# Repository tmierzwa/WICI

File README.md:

<p align="center"><picture><source media="(prefers-color-scheme: dark)" srcset="media/logo/WICI-na-ciemnym.svg"></picture></p>

<h1 align="center">Łączność awaryjna, gdy milkną telefony</h1>

Gdy nie ma prądu, zasięgu komórkowego ani internetu, ludzie w schronieniu nadal muszą dać znać, że brakuje wody, ktoś potrzebuje lekarza albo trzeba kogoś przewieźć. **WICI to otwarty projekt stacji radiowej do takich krótkich zgłoszeń i odpowiedzi.** Stacje mają stać tam, gdzie w kryzysie gromadzą się ludzie, i łączyć się ze stanowiskiem odbiorczym, które wyznacza gmina.

Gospodarz schronienia wybiera na ekranie stacji kategorię potrzeby i liczbę osób, a stacja wysyła zgłoszenie radiem. Na ekranie widać potem, czy odbiorca zgłoszenie zapisał, czy dyżurny je przeczytał i czy zapadła decyzja o pomocy. Każda włączona stacja przekazuje też wiadomości sąsiednich stacji, więc zgłoszenia docierają dalej niż zasięg jednego radia.

<p align="center"><sub>Wizualizacja koncepcyjna stacji według dzisiejszych założeń; <a href="hardware/obudowa/README.md">obudowa i render</a>, <a href="hardware/obudowa/render/stacja-materialy.png">pełna rozdzielczość</a>.</sub></p>

Stację można wypróbować w przeglądarce. [Symulator](https://wici.net.pl/symulator/) uruchamia ten sam program, który ma działać w prawdziwej stacji, razem z ćwiczeniami dla gospodarza i stanowiskiem odbiorczym. Uwagi można zgłosić przyciskiem „Zgłoś uwagę” w symulatorze albo [formularzem](https://github.com/tmierzwa/WICI/issues/new?template=uwaga-symulator.yml).

**Projekt jest na etapie prototypu (wersja 0.5). Dwa prototypy stacji są w montażu, a żadnej stacji nie sprawdzono jeszcze w terenie.** Dokumentacja, obliczenia i kod są otwarte. Pełny opis pomysłu, scenariuszy i ograniczeń jest na stronie [wici.net.pl](https://wici.net.pl/).

## Jak to ma działać

Stacja ma ekran, przyciski, antenę i ogniwa AA. Na ogniwach ma pracować co najmniej 48 godzin, a ze źródła 12 V dłużej. Zasięg i czas pracy trzeba jeszcze potwierdzić pomiarami.

W schronieniu stacja działa sama, bez komputera. Później będzie można podłączyć do niej laptop z wygodniejszym panelem, a przez router Wi-Fi udostępnić mieszkańcom lokalną stronę do zgłoszeń z telefonu, bez instalowania aplikacji. Na stanowisku odbiorczym komputer jest obowiązkowy: dyżurny przyjmuje na nim zgłoszenia i przekazuje je służbom.

Sieć trzeba przygotować z gminą i służbami przed kryzysem: zamontować anteny, sprawdzić trasy radiowe i uzgodnić dyżury. WICI ma uzupełniać lokalny system ochrony ludności. Nie zastępuje numeru 112 ani organizacji pomocy.

Pilotaż ma się odbyć na stacjach z ESP32-S3 i radiem LoRa SX1262, w profilu LoRa SF7 na kanale 869,525 MHz. Własny profil radiowy P1 (układy CC1120 i S2-LP), stanowiska deweloperskie i projekt własnej płytki R02 wstrzymano 8 października 2026 r. (F99); opisuje je [archiwum](docs/archiwum/README.md).

## Gdzie jesteśmy

Stan na 9 listopada 2026 r. Plan ma osiem kroków, a każdy ma warunek wejścia i wynik ([kolejność prac](docs/concept/08-plan-weryfikacji-i-decyzje.html#kolejnosc-prac)).

- **Krok 1, radia testowe: wykonany.** Dwa gotowe zestawy Seeed 102010611 (XIAO ESP32-S3 z Wio SX1262) wymieniły przy stole 100 ze 100 ramek w obie strony. W budynku, przy mocy 0 dBm, trasa około 20 m przez dwie ściany też dała 100/100, a dwie trudniejsze trasy były na granicy zasięgu tego profilu ([wyniki](hardware/radio-pair/evidence/range-r0-2026-10-10.txt)). Od 2 listopada te same zestawy z obrazem `xiao` służą do prób protokołu łącza WICI-Link v3 przy stole ([procedura](hardware/xiao-wici/README.md)).
- **Krok 2, radia RNode przy stole: wykonany.** 2 listopada dwa zestawy RAK19007 z RAK4631 (nRF52840 i SX1262) z oficjalnym firmware RNode 1.86 i Reticulum w Pythonie przeszły po 10 z 10 prób `rnprobe` w każdą stronę, w SF7 i w SF8. IFAC odrzucił radio z innym hasłem ([wyniki](hardware/rnode/evidence/krok2-2026-11-02.txt)). Wgranie firmware wymagało dwóch obejść ([radia RNode](hardware/rnode/README.md)). Obie instancje Reticulum działały na jednym laptopie, a jedyną drogą między nimi było radio. Zostały pomiar mocy na złączu przy 13 dBm i sprawdzenie, co RNode robi po przekroczeniu limitu czasu nadawania. Te same radia posłużą do pomiaru zasięgu (kroki 3 i 5) i do sprawdzenia zgodności prototypu (krok 4).
- **Krok 4, prototyp na płytce v1: w montażu.** Pięć płytek v1 (dawniej N1) z JLCPCB, części, panele i moduły autor kupił sam ([zamówienie](hardware/dev-bench/przed-produkcja.md#zamówienie-2026-10-10-l0)). Dwie płytki z zamontowanym SMD są u wykonawcy, [pw-lab.pl](https://pw-lab.pl/), który montuje i uruchamia je według [zlecenia](hardware/l0-diagnostic/ZLECENIE.md) i [instrukcji z diagnozą usterek](hardware/l0-diagnostic/MONTAZ-I-TESTY.md); trzy płytki są gołe. Najpierw powstanie jeden prototyp z programem diagnostycznym `l0-0.5`, drugi dopiero po udanym uruchomieniu pierwszego. Montaż pierwszego zaczął się 27 października i pokazał, że taśma panelu nie mieści się w obrysie płytki (F118). Panel mocuje się poza obrysem. Pierwsza sztuka (P001) jest zmontowana od 1 listopada i przeszła u wykonawcy pierwsze pomiary programem diagnostycznym (szyny zasilania, magistrala SPI, prąd nadawania); jego uwagi weszły do instrukcji. Poprawiony projekt v1.1 jest na `main`; nie jest do zamówienia, bo służy jako baza dla v2.
- **Program stacji.** Obrazy stacji mają własny rdzeń Reticulum z LXMF ([opis](firmware/reticulum-core.md)). Rdzeń jest domyślny, a port microReticulum zostaje w osobnych obrazach `*-port` do etapu rdzenia 6-5, który go usunie. Sprawdzono go na komputerze (zgodność z Reticulum i LXMF w Pythonie, fuzzing), ale nie na płytce. Próby 1–8 na płytkach są warunkiem pilotażu i wydania, ale nie scalania zmian. Obraz `l0` (`l0-0.6`, z portem `l0-port`, `l0-0.7`) ma własny sterownik SX1262 w profilu LoRa pilotażu, polecenia pomiarowe i tryb pracy do badań EMC ([opis](firmware/docs/prototyp-l0-i-xiao.md#stacja-l0-l0)); na płytce jeszcze nie działał. Interfejs LoRa w stosie Reticulum, zgodny z radiem RNode, przechodzi próby na komputerze z `RNodeInterface` przez emulator radia ([zgłoszenie 22](https://github.com/tmierzwa/WICI/issues/22)); próba z radiem RNode na prototypie jest w kroku 4. Od 2 listopada program ma też własny protokół łącza [WICI-Link v3](docs/spec/wici-link.md), który ma zastąpić Reticulum jako domyślny nośnik w sieci stacji, jeśli spełni warunek decyzji D21 ([warunek przyjęcia](docs/spec/transport.md#warunek-przyjęcia)). Na dwóch zestawach XIAO, przez jeden przeskok, 50 z 50 zgłoszeń dostało RECEIVED w około 5,5 min, bez ponowień ([wyniki](hardware/xiao-wici/evidence/xiao-zestaw-2026-11-03.md)). D21 rozstrzygnie próba na RAK4631 i prototypie. Brakuje funkcji potrzebnych przed pierwszymi stacjami w terenie ([zgłoszenie 23](https://github.com/tmierzwa/WICI/issues/23)).
- **Kroki 5–8.** Stacje pilotażowe powstaną na płytce v2 z linii prototypu (ESP32-S3-DevKitC, Wio SX1262, panel Sharp, FRAM, przyciski) z dodanym torem zasilania z ogniw AA i z 12 V: osiem stacji zamawianych w pełni zmontowanych w JLC, z modułami, obudową i anteną poza zamówieniem. Przed pracą w terenie zespół bada je według norm zharmonizowanych (D20). Wstępny schemat i rozmieszczenie v2 już są ([płytka v2](hardware/plytka-v2/README.md)), a sprawność przetwornicy 3,3 V sprawdzi osobna [płytka testowa](hardware/przetwornica-3v3/README.md); projekt v2 zamyka się po kroku 4. Pomiar w gminie (krok 5) wymaga gminy pilotażowej i wskazanych budynków. Pilotaż trwa co najmniej 3 miesiące, w tym zimę. O wyrobie, czyli stacji WICI, decyduje się po pilotażu.

Zakres prototypu (przygotowany do wyceny, dziś podstawa zlecenia montażu) i zasady wyboru dokumentów opisują [dokumenty przygotowania testów](output/README.md). Instrukcje bieżących prób są w katalogu [hardware](hardware/README.md).

### Kolejność prac

| Krok | Co | Stan |
|---|---|---|
| 1. Radia testowe | wstępna próba radia | wykonany |
| 2. Radia RNode przy stole | RNode na dwóch RAK4631, Reticulum na laptopach, `rnprobe` | wykonany |
| 3. Pomiar ogólny | zasięg na własnym terenie, SF7 i SF8, 13 dBm | do zrobienia |
| 4. Prototyp na płytce v1 | odbiór, program stacji, interfejs LoRa, zgodność z RNode, próby 1–8 rdzenia | w montażu |
| 5. Pomiar w gminie | trzy połączenia, dzień i wieczór | wymaga gminy i kroku 3 |
| 6. Stacje pilotażowe na płytce v2 | projekt v2, 8 stacji (pierwsze 2 jako prototypy v2), badania zgodności na wersji ostatecznej | po kroku 4 |
| 7. Pilotaż | ćwiczenie przy stole, potem ≥3 miesiące pracy | po kroku 6 |
| 8. Wyrób | stacja WICI | decyzja po pilotażu |

Kroki 3 i 4 idą równolegle. Do gminy nie jedzie się z niesprawdzonym sprzętem, więc gmina wchodzi w kroku 5. Pełny opis, z warunkami wejścia i wynikami, jest w [rozdziale 08 koncepcji](docs/concept/08-plan-weryfikacji-i-decyzje.html#kolejnosc-prac).

## Partnerzy projektu

- [pw-lab.pl](https://pw-lab.pl/): montaż, testy oraz diagnoza usterek prototypu stacji.

Firmy, gminy i organizacje, które chcą pomóc sprzętem, próbami albo wiedzą, mogą pisać na [kontakt@wici.net.pl](mailto:kontakt@wici.net.pl).

## Jak możesz pomóc

Najbliższy cel to pomiar zasięgu radiami RNode, a równolegle odbiór prototypu i pierwsza wymiana zgłoszeń z radiem RNode. Potem próby w prawdziwych miejscach. Przyda się doświadczenie w radiu i antenach, w programowaniu ESP32-S3 i SX1262 oraz w organizacji pomocy w gminie.

Można też pomóc bez sprzętu: sprawdzić obliczenia zasięgu, energii i ruchu radiowego, uprościć kartę obsługi albo poprawić tłumaczenia, zwłaszcza ukraińskie.

Konkretne zadania opisuje [CONTRIBUTING.md](CONTRIBUTING.md#od-czego-zacząć). Jeśli chcesz podjąć któreś z nich albo zgłosić błąd, otwórz [zgłoszenie (Issue)](https://github.com/tmierzwa/WICI/issues). Drobne poprawki możesz od razu przesłać jako PR.

## Co jest w repozytorium

| Katalog | Zawartość |
|---|---|
| [docs/concept](docs/concept/index.html) | Koncepcja: potrzeby, scenariusze, dostępne rozwiązania, architektura, wykonalność, zagrożenia, plan prób i otwarte decyzje; [strona online](https://wici.net.pl/) |
| [docs/spec](docs/README.md) | Specyfikacja stacji, warunki odbioru i lista części |
| [firmware](firmware/README.md) | Program stacji ze stosem Reticulum (własny rdzeń z LXMF) dla prototypu (`l0`: ESP32-S3-DevKitC-1 + Wio-SX1262 na płytce v1, profil LoRa); obrazy `bench-*` wstrzymanego wariantu (stanowiska deweloperskie, profil P1) i obrazy `*-port` z portem microReticulum; skompilowane, jeszcze nie uruchomione na sprzęcie |
| [software/reference](software/reference/README.md) | Model wiadomości i potwierdzeń z testami; obliczenia zasięgu, energii i czasu nadawania |
| [software/laptop](software/laptop/README.md) | Aplikacja laptopa z pamięci USB (Windows, macOS, Linux): przygotowanie stacji przez USB (etap 1) i zaszyfrowana baza (etap 2, warstwa bazy); [plan](software/laptop/PLAN.md) kolejnych etapów |
| [software/simulator](software/simulator/README.md) | Symulator stacji w przeglądarce: obraz bench-b oprogramowania stacji (te same źródła i flagi) na wirtualnej płytce ESP32-S3 z emulacją S2-LP, FRAM i Sharp, węzeł i stanowisko odbiorcze, panel płytki v1 (dawniej N1) i dawnej płytki R02 w skali, ćwiczenia gospodarza; [online](https://wici.net.pl/symulator/) |
| [hardware](hardware/README.md) | Radia testowe (`radio-pair`), program diagnostyczny prototypu (`l0-diagnostic`), płytka v1 prototypu (`dev-bench`), obudowa oraz projekt R02 (wstrzymany; materiał do płytki v2 i do wyrobu) |
| [media/film](media/film/README.md) | Dwa filmy o projekcie: około 4,5 min i 60 s |
| [media/infografika](media/infografika/README.md) | Infografika do mediów społecznościowych: post i Stories (PL, EN) |
| [media/logo](media/logo/README.md) | Znak WICI i ikony |
| [tools](docs/development.md) | Kontrola repozytorium i tworzenie paczki źródłowej |

Do sprawdzenia repozytorium wystarczy Python 3.12 lub nowszy:

```sh
python3 -m unittest discover -s software/reference -v
python3 -m unittest discover -s tests -v
python3 tools/verify_repository.py
```

Te same kontrole uruchamia się przed zgłoszeniem zmiany (PR); szczegóły są w [CONTRIBUTING.md](CONTRIBUTING.md#kontrole-przed-pr). Środowisko CAD opisuje [docs/development.md](docs/development.md).

## Kto za tym stoi

Projekt prowadzi na razie jedna osoba: [@tmierzwa](https://github.com/tmierzwa). Gminy, służby, krótkofalowcy i media mogą pisać na [kontakt@wici.net.pl](mailto:kontakt@wici.net.pl). Sprawy techniczne najlepiej zgłaszać w [Issues](https://github.com/tmierzwa/WICI/issues).

Duża część analiz, obliczeń i dokumentacji powstała z pomocą asystenta AI (Claude). Takie commity mają wiersz `Co-Authored-By`. Autor przegląda każdą zmianę. Obliczenia i założenia prawne czekają na niezależny przegląd, a wyniki modelu trzeba potwierdzić pomiarami.

## Licencje

Projekt jest otwarty, a licencje dopuszczają zastosowania komercyjne. Kod jest na licencji MIT, konstrukcja na CERN-OHL-P-2.0, a dokumentacja na CC-BY-4.0.

Wyjątkiem jest rdzeń Reticulum stacji (`firmware/lib/reticulum_core/`). Jako utwór zależny od Reticulum jest na [licencji Reticulum](LICENSES/LicenseRef-Reticulum.txt). Ta licencja dodaje do warunków MIT zakaz użycia w systemach, których funkcją jest celowe szkodzenie ludziom, i zakaz użycia przy tworzeniu zbiorów do trenowania AI, więc nie jest licencją open source w rozumieniu OSI. Obraz stacji z rdzeniem podlega jej jako całość.

Szczegóły są w [LICENSE.md](LICENSE.md). Podatności zgłaszaj prywatnie według [SECURITY.md](SECURITY.md). Obowiązuje [kodeks postępowania](CODE_OF_CONDUCT.md).

## In English

WICI is an open project for an emergency radio station for shelters in Poland. It is meant to carry short requests for help when power, mobile networks and the internet are down. A station with a screen, buttons and AA cells would send requests, show acknowledgements and decisions, and relay neighbouring stations' messages. The receiving post needs a computer and an agreed procedure for passing requests to emergency services.

The project is at the **prototype stage (0.5)**: two prototypes are being assembled by a contractor, and no station has been field-tested. The plan has eight steps. Two RNode radios (RAK4631) were ordered on 29 October 2026 for bench tests and range measurements with Reticulum on two laptops; next come the prototype on the v1 board, a measurement in a municipality, eight pilot stations on a v2 board (ESP32-S3 module with an SX1262 LoRa radio) and a pilot of at least three months, including winter. The project's own FSK profile and custom board were put on hold on 8 October 2026. Range and battery life remain to be measured. Code, hardware and documentation are under permissive licences; the station's Reticulum core is under the Reticulum License, which is not OSI open source (see [LICENSE.md](LICENSE.md)).

One person currently maintains the project with AI assistance. Project partner: [pw-lab.pl](https://pw-lab.pl/), assembly, testing and fault diagnosis of the station prototype. Help with radio, firmware, civil protection, field testing and independent review is welcome. Documentation is in Polish; issues and pull requests in English are welcome. See [CONTRIBUTING.md](CONTRIBUTING.md#in-english). Contact: [kontakt@wici.net.pl](mailto:kontakt@wici.net.pl).

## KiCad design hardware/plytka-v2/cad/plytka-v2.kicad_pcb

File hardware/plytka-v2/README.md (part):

# WICI: płytka v2, schemat wstępny

**Status 2026-11-11: komplet ścieżek z czystym DRC po trzech niezależnych przeglądach ([Ścieżki](#ścieżki-2026-11-10)), pliki produkcyjne po końcowym przeglądzie i sprawdzeniu podglądu JLC ([Części w JLC i pliki produkcyjne](#części-w-jlc-i-pliki-produkcyjne-2026-11-10)). Zamówienie dwóch prototypów czeka na pomiar przetwornicy 3,3 V ([Przed zamówieniem](#przed-zamówieniem)); przymiarka z prawdziwą skrzynką odbędzie się po zamówieniu prototypów, z ryzykiem poprawki rozmieszczenia w następnej wersji. Pierwsze uruchomienie: [uruchomienie.md](uruchomienie.md).** Schemat zbiera w jednym projekcie KiCad płytkę v1.1 prototypu i tor zasilania stacji pilotażowej ([elektronika](../../docs/spec/elektronika.md#stacja-pilotażowa)). Wartości elementów pochodzą z [projektu zasilania](../r02/zasilanie.md) i z [płytki testowej przetwornicy](../przetwornica-3v3/README.md). Obrys i rozmieszczenie są wstępne. Obrys, otwory i złącza na dolnej krawędzi są dopasowane do modelu STEP obudowy Hammond 1599KBAT ([Dopasowanie do obudowy](#dopasowanie-do-obudowy-2026-11-09)). Przymiarka, pomiary na prototypach i krok 4 mogą jeszcze zmienić rozmieszczenie w następnej wersji ([Przed zamówieniem](#przed-zamówieniem)).

| Plik | Zawartość |
|---|---|
| [schemat.pdf](schemat.pdf) | schemat (arkusz A0, połączenia przez etykiety sieci, jak w v1) |
| [polaczenia.md](polaczenia.md) | sygnały MCU i wszystkie sieci |
| [uruchomienie.md](uruchomienie.md) | pierwsze uruchomienie zmontowanego prototypu krok po kroku, z warunkami przerwania |
| [bom.csv](bom.csv) | lista części z producentami, numerami i numerami LCSC, tam gdzie są już wybrane |
| `cad/plytka-v2.kicad_sch`, `cad/plytka-v2.kicad_pcb`, `cad/plytka-v2.kicad_dru` | projekt KiCad 10.0.6: schemat, płytka 4-warstwowa ze ścieżkami i reguły projektu |
| `checks/erc.json`, `checks/netlist.xml`, `checks/drc.json` | ERC (0 naruszeń), lista połączeń i DRC (0 naruszeń poza sitodrukiem, 0 niepołączonych; [Ścieżki](#ścieżki-2026-11-10)) |
| `checks/routing*.dsn`, `checks/routing*.ses`, `checks/routing*.ses.sha256`, `checks/routing*.log`, `checks/routing-anchors.json` | dla każdego etapu routera: zadanie dla Freeroutingu, zachowana sesja ścieżek, suma zadania, z którego powstała, i dziennik przebiegu; lista punktów, w których router może dołączyć do miedzi ręcznej |
| [render-sciezki-gora.png](render-sciezki-gora.png), [render-sciezki-spod.png](render-sciezki-spod.png) | render płytki ze ścieżkami od góry i od spodu |
| `tools/design.py` | jedyne źródło: części, piny, sieci i sprawdzenia przydziału pinów |
| `tools/make_pcb.py` | obrys, otwory i rozmieszczenie: założenia, położenia stałe i obszary bloków |
| `tools/route_pcb.py`, `tools/route.sh` | klasy sieci, reguły, warstwy, miedź ręczna i płaszczyzny, zadania dla routera; uruchomienie Freeroutingu etapami |

Odtworzenie: `hardware/plytka-v2/tools/build.sh` (KiCad 10.0.6). Skrypt sprawdza przydział pinów, generuje schemat, BOM i listę połączeń, uruchamia ERC, rysuje PDF, rozmieszcza elementy na płytce, dokłada miedź ręczną, wczytuje zachowaną sesję ścieżek (gdy pasuje do zadania) i uruchamia DRC. Plików w `cad/` nie edytuje się ręcznie.

## Co zmienia się względem v1.1

| Blok | v1.1 (prototyp L0) | v2 |
|---|---|---|
| MCU | DevKitC w J5/J6, zasilana z USB | ta sama DevKitC v1.1 (N8R8) w J5/J6, zasilana przez piny 3V3 z przetwornicy; pin 5V wolny |
| Radio | Wio na przewodach obok płytki | Wio w gniazdach J8/J9 (2 × 1x7, 2,54 mm), zasilanie przez zworkę pomiarową JP3, przy module C1, C2 i RXEN 10 kΩ (R64); SCK za R18, jak ekran i FRAM |
| Gniazda TI, ST, Nordic | J1–J4, J9, J10, JP3, R17, otwory Arduino | wypadają |
| USB do laptopa | złącze micro USB DevKitC | gniazdo USB-C J4 bez zasilania z VBUS (VBUS tylko na bramkę Q12 wykrywania laptopa), CC1 i CC2 przez 5,1 kΩ, ochrona ESD U8 |
| Ekran, FRAM, dioda | bez zmian | bez zmian (te same oznaczenia) |
| Przyciski i CISZA | B3F na płytce (SW1–SW4), przełącznik na płytce (SW5) | panelowe PV6F240SS i 100SP1T8B13M1QEH z osłoną GT-4R na wiązkach do J10 i J11, ochrona ESD U9 i filtry RC ([front w wariancie 2](#front-w-wariancie-2-2026-11-09)) |
| Brzęczyk | z pinu 5V DevKitC przez JP2 | z szyny 5 V ekranu (U2), bo pin 5V DevKitC jest martwy przy zasilaniu przez 3V3 |
| Pomiar | VTEST (J12) i złącze analizatora J11 | J11, J12 i dzielnik VTEST wypadają; pomiar ogniw i 12 V na GPIO4 i GPIO5 |
| Zasilanie | brak | ogniwa 4 × AA i 12 V na wspólną szynę VSYS, sterownik przycisku, przetwornica 3,3 V |

## Tor zasilania

```text
J1 4×AA ─ R40 1 Ω ─ D7 Schottky ─────────────────────────────┬─ VSYS ─ C50 ─ U7 LTC3115-1 (RUN ← Q9) ─ +3V3
J2 12 V ─ F1 T1A ─ D4 TVS 33 V ─ Q2 ─(wspólny dren)─ Q3 ───────┘
                                  └ U5 LM74800-Q1: DGATE, HGATE, OVP 16,8 V, EN/UVLO ← dzielnik przez Q4
suma diodowa D8 (ogniwa) i D9 (wspólny dren przez R46, C35, D10 33 V) ─ VCTL ─ U6 LTC2955-2 ─ Q8 ─ szyna ON
V12 ─ D13 BAS116H ─ R70/R71 ─ ON U6 (zbocze narastające przez około 9 V włącza)
VCTL ─ R48/D16 ─ KILL U6 ← Q11 ← GPIO47
ON ─ Q5 ─ Q4: dzielnik 12 V (EN/UVLO U5 i ADC)    ON ─ Q10 ─ Q9: RUN przetwornicy z VSYS
```

- **Włączenie z samego 12 V (bez ogniw):** wspólny dren Q2/Q3 dostaje napięcie przez diodę podłożową Q2 także przy wyłączonym U5 (karta LM7480-Q1, 9.4). Z niego przez R46 i D9 zasilany jest sterownik U6. Naciśnięcie przycisku (J3) daje szynę ON. ON podłącza przez Q4 dzielnik 12 V do EN/UVLO U5, a przy V12 ≥11,9 V (najwyżej 12,3 V) U5 włącza Q3 i zasila VSYS. Równolegle ON przez Q10 i Q9 podaje VSYS na RUN przetwornicy.
- **Samoczynne włączenie z 12 V:** stacja ma być włączona zawsze, kiedy to możliwe (decyzja 4). Dzielnik R70/R71 (280 kΩ / 30,1 kΩ, 0,1%) podaje 12 V przez diodę D13 (BAS116H) na wejście ON sterownika. Zbocze narastające przy około 8,2–9,6 V włącza stację jak przycisk. To szacunek: próg ON 0,76–0,84 V (karta) × 10,28–10,32 (R70/R71 0,1%) daje 7,81–8,67 V, a do tego dochodzi spadek D13 przy około 27 µA, którego karta BAS116H nie podaje. Przyjęto 0,4–0,9 V: górna granica to ≤0,9 V przy 1 mA z karty, mniej przy 27 µA i więcej na zimno do −20 °C; dolna z wykresu na gorąco z zapasem. Próba odbiorcza wymaga zbocza nie poniżej 8,0 V i najpóźniej przy 9,8 V. Przy odwróconym 12 V D13 blokuje, więc ON zostaje na około 0 V (upływ ≤80 nA), a nie na granicy −0,3 V z karty LTC2955. Próg leży poniżej napięcia każdego działającego źródła, więc każde podłączenie i każdy powrót 12 V po zaniku włącza stację, także akumulator 12,6 V w spoczynku i napięcie narastające powoli z panelu. Próg może leżeć poniżej progu włączenia UV: sterownik zostaje włączony i czeka, a U5 załącza 12 V, gdy napięcie dojdzie do około 11,9 V. W obudowie TSOT-23 opadające zbocze ON nic nie robi, a stałe 12 V nie włącza stacji z powrotem po wyłączeniu przyciskiem. Wyłączenie ręczne trwa więc do następnego podłączenia albo powrotu 12 V; rozruch silnika, przy którym napięcie spada poniżej około 9 V, też włączy stację. Dzielnik pobiera z podłączonego 12 V około 37 µA także przy wyłączonej stacji.
- **Podtrzymanie bez 3,3 V:** KILL jest podciągnięty z VCTL, czyli z zasilania U6 (R48 470 kΩ, Zener D16 5,1 V wobec 6 V dopuszczalnych), a nie z +3V3 ani z szyny ON. Gdy 12 V spadnie poniżej progu UV bez ogniw, znika 3,3 V, ale sterownik zostaje włączony i stacja wraca sama, gdy tylko 12 V da się znów użyć. Po całkowitym zaniku 12 V bez ogniw KILL idzie za VCTL do około 0,8 V, więc U6 traci stan przez podnapięcie zasilania (0,8–1,3 V), a nie przez KILL. Po powrocie 12 V startuje z wysokim ON i włącza stację po około 1 s (karta LTC2955, „ON Pin Initial Turn-On”). Z KILL na szynie ON zanik trwający 0,2–1,6 s kończyłby się w blokadzie 0,6–1,4 s po zwolnieniu EN i stacja zostałaby wyłączona. Przy VCTL około 3,6 V (słabe ogniwa) KILL zostaje powyżej 2 V przy upływie Zenera 2 µA i Q11 0,5 µA w 25 °C. Czekający sterownik pobiera z rozładowanego akumulatora do około 0,55 mA (U5, dzielnik UV i R78, który przy szynie ON około 11 V bierze około 0,1 mA).
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
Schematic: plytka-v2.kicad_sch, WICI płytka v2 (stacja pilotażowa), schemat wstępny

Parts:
BZ1: CEM-1203(42); MagneticBuzzer_ProSignal_ABT-410-RC; MPN CEM-1203(42)
C1, C4, C8, C9, C47: 10u; C_0805_2012Metric; MPN CL21A106KAYNNNE
C2, C3, C6, C7, C11, C12, C31, C33, C34, C36, C44, C45, C46, C60, C61, C62, C63, C64: 100n; C_0805_2012Metric; MPN CC0805KRX7R9BB104
C10: 100p; C_0805_2012Metric; MPN CL21C101JBANNNC
C13: 100u; C_1210_3225Metric; MPN LMK325ABJ107MM-P
C30, C38: 100n; C_0805_2012Metric; MPN CL21B104KCFNNNE
C32: 27n; C_0805_2012Metric; MPN CC0805KRX7R9BB273
C35: 1u; C_0805_2012Metric; MPN CL21B105KBFNNNE
C37: 2u2; C_0805_2012Metric; MPN CL21B225KAFNNNE
C39, C65: 10n; C_0805_2012Metric; MPN CL21B103KBANNNC
C40, C41: 10u; C_1210_3225Metric; MPN CC1210KKX7R9BB106
C42, C43: 22u; C_1210_3225Metric; MPN CS3225X5R226K160NRL
C48, C51: 82p; C_0805_2012Metric; MPN CC0805JRNPO9BN820
C49: 3n9; C_0805_2012Metric; MPN CC0805KRX7R9BB392
C50: 100u 25V; CP_Radial_D8.0mm_P3.50mm; MPN UKL1E101MPD
C52: 1n; C_0805_2012Metric; MPN CC0805KRX7R9BB102
C53: 470n; C_0805_2012Metric; MPN CL21B474KBFNNNE
D1: ALARM; LED_D5.0mm; MPN WP7113ID
D2: 1N4148W; D_SOD-123; MPN 1N4148W
D4: SMBJ33CA; D_SMB; MPN SMBJ33CA
D5, D12, D14, D15, D17: BZT52C15; D_SOD-123; MPN BZT52C15-7-F
D6, D11: BAV199; SOT-23; MPN BAV199,215
D7: RB168MM-40; D_SOD-123F; MPN RB168MM-40TR
D8, D9, D13: BAS116H; D_SOD-123F; MPN BAS116H,115
D10: BZT52C33; D_SOD-123; MPN BZT52C33-7-F
D16: BZT52C5V1; D_SOD-123; MPN BZT52C5V1
D18, D19: TPD1E10B09; Texas_DPY0002A_0.6x1mm_P0.65mm; MPN TPD1E10B09DPYR
D20: SMBJ33CA; D_SMB; MPN SMBJ33CA; not fitted
F1: T1A; Fuseholder_Clip-5x20mm_Bel_FC-203-22_Lateral_P17.80x5.00mm_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; MPN 01110501Z
H1, H2, H3, H4, H5, H6: #4; MountingHole_3.5mm
J1: OGNIWA 4xAA; JST_XH_B2B-XH-A_1x02_P2.50mm_Vertical; MPN B2B-XH-A(LF)(SN)
J2: 12V; JST_XH_B2B-XH-A_1x02_P2.50mm_Vertical; MPN B2B-XH-A(LF)(SN)
J3: WYLACZNIK; JST_XH_B2B-XH-A_1x02_P2.50mm_Vertical; MPN B2B-XH-A(LF)(SN)
J4: USB-C DANE; USB_C_Receptacle_HRO_TYPE-C-31-M-12; MPN TYPE-C-31-M-12
J5: DEVKITC J1; PinSocket_1x22_P2.54mm_Vertical; MPN PPTC221LFBN-RC
J6: DEVKITC J3; PinSocket_1x22_P2.54mm_Vertical; MPN PPTC221LFBN-RC
J7: SHARP LS027B7DH01A; Hirose_FH12-10S-0.5SH_1x10-1MP_P0.50mm_Horizontal; MPN FH12-10S-0.5SH(55)
J8: WIO J1; PinSocket_1x07_P2.54mm_Vertical; MPN PPTC071LFBN-RC
J9: WIO J2; PinSocket_1x07_P2.54mm_Vertical; MPN PPTC071LFBN-RC
J10: PRZYCISKI; JST_XH_B5B-XH-A_1x05_P2.50mm_Vertical; MPN B5B-XH-A(LF)(SN)
J11: CISZA; JST_XH_B2B-XH-A_1x02_P2.50mm_Vertical; MPN B2B-XH-A(LF)(SN)
JP3: 3V3 RADIO; PinHeader_1x02_P2.54mm_Vertical; MPN 61300211121
L1: 4u7; L_Wuerth_WE-TPC-3816; MPN 744031004
L2: 15u; L_Bourns_SRP1038A; MPN SRP1038A-150M
Q1: MMBT3904; SOT-23; MPN MMBT3904
Q2, Q3: AO4292E; SOIC-8_3.9x4.9mm_P1.27mm; MPN AO4292E
Q4: SI2309CDS; SOT-23; MPN SI2309CDS-T1-GE3
Q5: 2N7002; SOT-23; MPN 2N7002,215
Q6, Q8, Q9: BSS84AK; SOT-23; MPN BSS84AK,215
Q7, Q10, Q11, Q12: BSS138; SOT-23; MPN BSS138LT1G
R1, R3, R12, R16, R32, R80, R81, R82, R83, R84: 1k; R_0805_2012Metric; MPN 0805W8F1001T5E
R2: 22R; R_1206_3216Metric; MPN 1206W4F220JT5E
R4, R33, R34, R35, R41, R43, R50, R53, R63, R72, R73, R75, R78: 100k; R_0805_2012Metric; MPN 0805W8F1003T5E
R5, R6, R7, R8, R9, R10, R11, R13, R19, R20, R47, R64, R76, R77: 10k; R_0805_2012Metric; MPN 0805W8F1002T5E
R18: 33R; R_0805_2012Metric; MPN 0805W8F330JT5E
R21, R36, R49, R54, R61, R74: 1M; R_0805_2012Metric; MPN 0805W8F1004T5E
R22: 309k; R_0805_2012Metric; MPN 0805W8F3093T5E
R30: 102k; R_0805_2012Metric; MPN RT0805BRD07102KL
R31: 8k06; R_0805_2012Metric; MPN RT0805BRD078K06L
R37: 221k; R_0805_2012Metric; MPN AR05BTCW2213
R38, R45: 10k; R_0805_2012Metric; MPN RT0805BRD0710KL
R39: 15k4; R_0805_2012Metric; MPN RT0805BRD0715K4L
R40: 1R; R_2512_6332Metric; MPN RC2512FK-071RL
R44: 39k; R_0805_2012Metric; MPN ARG05BTC3902
R46: 1k; R_2512_6332Metric; MPN RC2512FK-071KL
R48: 470k; R_0805_2012Metric; MPN 0805W8F4703T5E
R51, R55: 220k; R_0805_2012Metric; MPN 0805W8F2203T5E
R60: 47k5; R_0805_2012Metric; MPN RC0805FR-0747K5L
R62: 432k; R_0805_2012Metric; MPN 0805W8F4323T5E
R65, R66: 5k1; R_0805_2012Metric; MPN 0805W8F5101T5E
R67, R68: 20k; R_0805_2012Metric; MPN 0805W8F2002T5E
R70: 280k; R_0805_2012Metric; MPN RT0805BRD07280KL
R71: 30k1; R_0805_2012Metric; MPN RT0805BRD0730K1L
SW6: PRZYGOTOWANIE; SW_TH_Tactile_Omron_B3F-100x; MPN B3F-1000
U1: CY15B104QN-50SXI; SOIC-8_5.3x5.3mm_P1.27mm; MPN CY15B104QN-50SXI
U2: MCP1640; SOT-23-6; MPN MCP1640T-I/CHY
U3: TPS3840PH27; SOT-23-5; MPN TPS3840PH27DBVRQ1
U4: 74LVC1G32; SOT-23-5; MPN SN74LVC1G32DBVR
U5: LM74800-Q1; WSON-12-1EP_3x3mm_P0.5mm_EP1.5x2.5mm; MPN LM74800QDRRRQ1
U6: LTC2955ITS8-2; TSOT-23-8; MPN LTC2955ITS8-2#TRPBF
U7: LTC3115-1; LTC3115-1_FE20_CA; MPN LTC3115EFE-1#PBF
U8: USBLC6-2SC6; SOT-23-6; MPN USBLC6-2SC6
U9: TPD4E1U06DCKR; SOT-363_SC-70-6; MPN TPD4E1U06DCKR

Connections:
12V_IN: F1.1, J2.1
+3V3: C3.1, C8.1, C11.1, C12.1, C13.1, C42.1, C43.1, D6.2 (K), D11.2 (K), J5.1, J5.2, JP3.1, L1.1, R5.1, R6.1, R7.1, R8.1, R9.1, R10.1, R11.1, R20.1, R47.1, R61.1, R68.2, R75.1, U1.3 (~WP), U1.7 (~HOLD), U1.8 (VDD), U2.3 (EN), U2.6 (V_{IN}), U3.2 (VDD), U4.5 (VCC), U7.4 (PVOUT), U8.5 (VBUS)
+3V3_RF: C1.1, C2.1, J9.3, JP3.2
+5V: C4.1, C6.1, C9.1, C10.1, J7.6, J7.7, J7.8, R2.1, R21.1, U2.5 (V_{OUT})
BAT_IN: J1.1, Q6.2 (S), R40.1, R41.1
BAT_R: D7.2 (A), D8.2 (A), R40.2
BST_FB: C10.2, R21.2, R22.1, U2.4 (V_{FB})
BST_SW: L1.2, U2.1 (SW)
BTN_BACK: C63.1, J6.5, R8.2, R83.2
BTN_BACK_IN: J10.4, R83.1, U9.6 (IO5)
BTN_DOWN: C61.1, J6.8, R6.2, R81.2
BTN_DOWN_IN: J10.2, R81.1, U9.3 (IO2)
BTN_OK: C62.1, J6.9, R7.2, R82.2
BTN_OK_IN: J10.3, R82.1, U9.4 (IO3)
BTN_PREP: J5.6, R10.2, SW6.1
BTN_UP: C60.1, J6.7, R5.2, R80.2
BTN_UP_IN: J10.1, R80.1, U9.1 (IO1)
BUZZER: J5.8, R3.1
BZ_N: BZ1.2 (-), D2.2 (A), Q1.3 (C)
BZ_P: BZ1.1 (+), D2.1 (K), R2.2
CONV_BST1: C44.1, U7.16 (BST1)
CONV_BST2: C45.1, U7.15 (BST2)
CONV_CMP1: C49.2, R67.1
CONV_CMP2: C51.2, R68.1
CONV_FB: C48.1, C49.1, C51.1, R61.2, R62.1, U7.8 (FB)
CONV_RT: R60.1, U7.9 (RT)
CONV_SW1: C44.2, L2.2, U7.18 (SW1)
CONV_SW2: C45.2, L2.1, U7.3 (SW2)
CONV_VC: C48.2, R67.2, U7.7 (VC)
CONV_VCC: C47.1, U7.12 (VCC), U7.14 (PVCC)
DIV_EN: J5.14, Q7.1 (G), R43.1
FRAM_CS: J5.12, R20.2, U4.1
FRAM_CS_U1: U1.1 (~CS), U4.4
FRAM_GUARD: U3.1 (RESET), U4.2
GND: C1.2, C2.2, C3.2, C4.2, C6.2, C7.2, C8.2, C9.2, C11.2, C12.2, C13.2, C30.2, C32.2, C33.2, C34.2, C35.2, C36.2, C37.2, C38.2, C39.2, C40.2, C41.2, C42.2, C43.2, C46.2, C47.2, C50.2, C52.2, C53.2, C60.2, C61.2, C62.2, C63.2, C64.2, C65.2, D1.1 (K), D4.2 (A2), D6.1 (A), D10.2 (A), D11.1 (A), D14.2 (A), D15.2 (A), D16.2 (A), D17.2 (A), D18.2 (GND), D19.2 (GND), D20.2 (A2), J1.2, J2.2, J3.2, J4.A1 (GND), J4.A12 (GND), J4.B1 (GND), J4.B12 (GND), J4.SH (SHIELD), J5.22, J6.1, J6.21, J6.22, J7.9, J7.10, J7.MP (MountPin), J9.2, J10.5, J11.2, Q1.2 (E), Q5.2 (S), Q7.2 (S), Q10.2 (S), Q11.2 (S), Q12.2 (S), R4.2, R12.2, R13.2, R19.2, R22.2, R31.2, R36.2, R39.2, R43.2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
KILL_MCU: J6.17, Q11.1 (G), R72.1
LCD_CS: J5.7, J7.3, R13.1
LCD_DISP: C7.1, J5.9, J7.5, R19.1
LCD_EXTCOMIN: J5.10, J7.4
LED_A: D1.2 (A), R1.2
LED_ALARM: J5.11, R1.1
ON: Q8.3 (D), R35.1, R53.1, R78.1
ON_DIV: D13.1 (K), R70.1
PWM_SYNC: J6.15, R63.1, U7.19 (PWM/SYNC)
PWR_ENB: R50.2, U6.7 (~EN)
PWR_INT: J6.16, R47.2, U6.8 (INT)
PWR_KILL: D16.1 (K), Q11.3 (D), R48.2, U6.2 (KILL)
PWR_ON: C53.1, R70.2, R71.1, U6.1 (ON)
PWR_PB: C65.1, R84.2, U6.5 (PB)
PWR_PB_IN: D18.1 (I/O), J3.1, R84.1
PWR_TMR: C37.1, U6.3 (TMR)
Q1_B: Q1.1 (B), R3.2, R4.1
Q4_G: D5.2 (A), Q4.1 (G), R33.2, R34.1
Q5_D: Q5.3 (D), R34.2
Q5_G: D15.1 (K), Q5.1 (G), R35.2, R36.1
Q6_G: Q6.1 (G), Q7.3 (D), R41.2
Q8_G: D12.2 (A), Q8.1 (G), R49.2, R50.1
Q9_G: Q9.1 (G), Q10.3 (D), R51.2
Q10_G: D14.1 (K), Q10.1 (G), R53.2, R54.1
Q12_G: D17.1 (K), Q12.1 (G), R73.2, R74.1
RF_CS: J5.16, J8.4, R11.2
RF_GPIO0: J5.20, J8.2
RF_GPIO1: J6.18, J8.1
RF_GPIO3: J6.6, J8.5, R64.1
RF_RESET: J5.15, J8.3, R12.1
RUN: C52.1, Q9.3 (D), R55.1, U7.2 (RUN)
S12_CAP: C31.1, U5.11 (CAP)
S12_DGATE: Q2.4 (G), U5.1 (DGATE)
S12_DVDT: C32.1, R32.2
S12_EN: C39.1, R37.2, R38.1, U5.6 (EN/UVLO)
S12_HGATE: Q3.4 (G), R32.1, U5.8 (HGATE)
S12_OV: R30.2, R31.1, U5.5 (OV)
S12_SW: R30.1, U5.4 (SW)
SPI_MISO: J5.19, J9.5, U1.2 (SO)
SPI_MOSI: J5.17, J7.2, J9.4, U1.5 (SI)
SPI_SCK: J7.1, J9.6, R18.2, U1.6 (SCK)
SPI_SCK_DEVKIT: J5.18, R18.1
SW_CISZA: C64.1, J6.4, R9.2, R16.2
SW_COM: D19.1 (I/O), J11.1, R16.1
USB_CC1: J4.A5 (CC1), R65.1
USB_CC2: J4.B5 (CC2), R66.1
USB_DN: J4.A7 (D-), J4.B7 (D-), J6.20, U8.3 (I/O2), U8.4 (I/O2)
USB_DP: J4.A6 (D+), J4.B6 (D+), J6.19, U8.1 (I/O1), U8.6 (I/O1)
USB_LAPTOP: J5.13, Q12.3 (D), R75.2
USB_VBUS: J4.A4 (VBUS), J4.A9 (VBUS), J4.B4 (VBUS), J4.B9 (VBUS), R73.1
V12_F: C38.1, D4.1 (A1), D5.1 (K), D13.2 (A), D20.1 (A1), F1.2, Q2.1 (S), Q2.2 (S), Q2.3 (S), Q4.2 (S), R33.1, U5.2 (A)
V12_FLT: C35.1, D9.2 (A), D10.1 (K), R46.2
V12_MID: C30.1, C31.2, Q2.5 (D), Q2.6 (D), Q2.7 (D), Q2.8 (D), Q3.5 (D), Q3.6 (D), Q3.7 (D), Q3.8 (D), R46.1, U5.3 (VSNS), U5.10 (VS), U5.12 (C)
V12_SW: Q4.3 (D), R37.1
VAA_SW: Q6.3 (D), R44.1
VCTL: C36.1, D8.1 (K), D9.1 (K), D12.1 (K), Q8.2 (S), R48.1, R49.1, U6.6 (VIN)
VSYS: C40.1, C41.1, C46.1, C50.1, D7.1 (K), Q3.1 (S), Q3.2 (S), Q3.3 (S), Q9.2 (S), R51.1, U5.9 (OUT), U7.13 (VIN), U7.17 (PVIN)
V_12_ADC: C33.1, J5.5, R76.2
V_12_DIV: D6.3 (COM), R38.2, R39.1, R76.1
V_AA_ADC: C34.1, J5.4, R77.2
V_AA_DIV: D11.3 (COM), R44.2, R45.1, R77.1

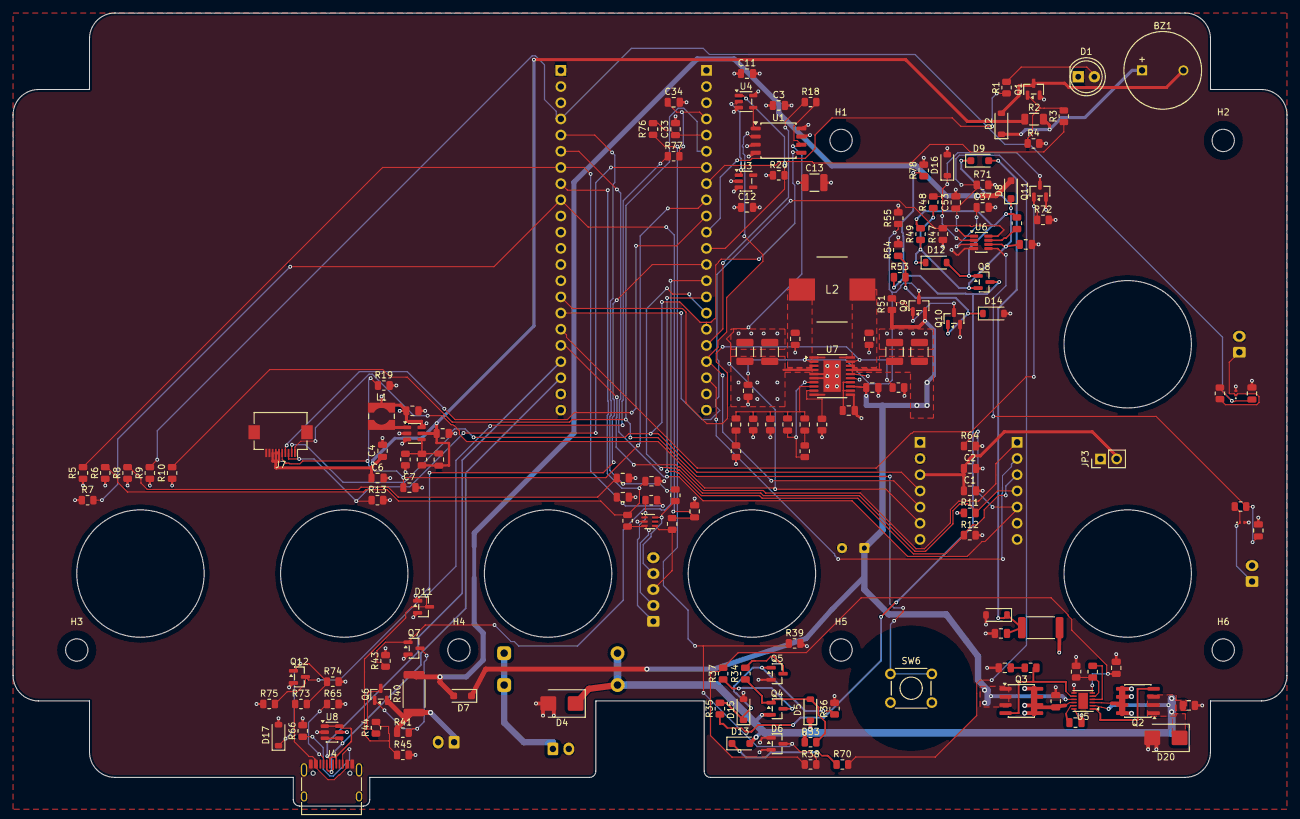
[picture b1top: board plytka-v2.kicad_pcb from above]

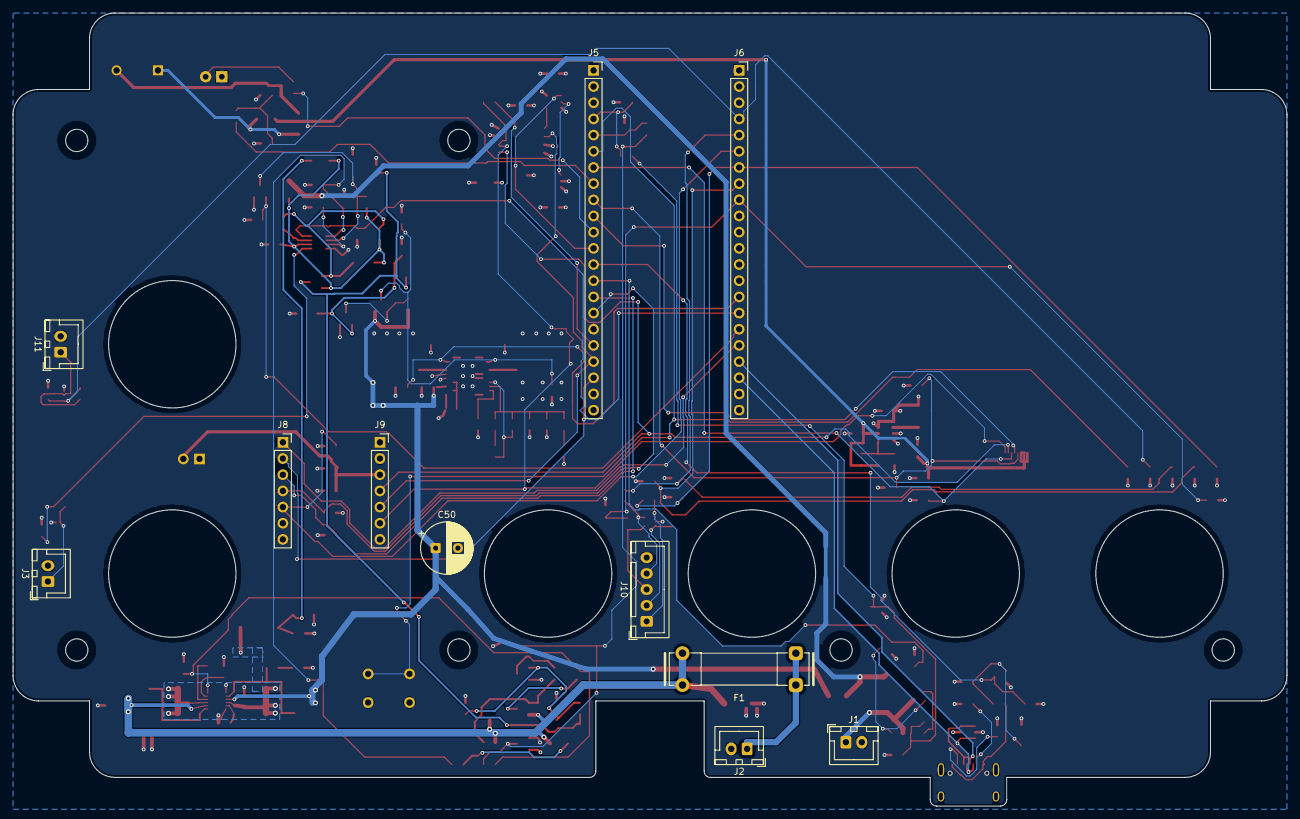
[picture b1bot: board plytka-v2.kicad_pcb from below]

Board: 4 copper layers, 200.0 x 124.5 mm, 171 parts (11 on the bottom side), 96 nets.

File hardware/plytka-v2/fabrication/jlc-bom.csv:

Comment,Designator,Footprint,LCSC Part #
DEVKITC J1 / DEVKITC J3 (HC-PM254-8.5H-1x22PZ),"J5,J6",PinSocket_1x22_P2.54mm_Vertical,C41376161
33R (0805W8F330JT5E),R18,R_0805_2012Metric,C17634
WIO J1 / WIO J2 (HX PM2.54-1x7P ZC-Y),"J8,J9",PinSocket_1x07_P2.54mm_Vertical,C22438157
3V3 RADIO (61300211121),JP3,PinHeader_1x02_P2.54mm_Vertical,C2915055
10u (CL21A106KAYNNNE),"C1,C4,C8,C9,C47",C_0805_2012Metric,C15850
100n (CC0805KRX7R9BB104),"C2,C6,C7,C3,C11,C12,C60,C61,C62,C63,C64,C31,C33,C34,C36,C44,C45,C46",C_0805_2012Metric,C49678
10k (0805W8F1002T5E),"R11,R64,R13,R19,R20,R5,R6,R7,R8,R9,R10,R76,R77,R47",R_0805_2012Metric,C17414
1k (0805W8F1001T5E),"R12,R80,R81,R82,R83,R16,R1,R3,R32,R84",R_0805_2012Metric,C17513
USB-C DANE (TYPE-C-31-M-12),J4,USB_C_Receptacle_HRO_TYPE-C-31-M-12,C165948
5k1 (0805W8F5101T5E),"R65,R66",R_0805_2012Metric,C27834
100k (0805W8F1003T5E),"R73,R75,R4,R33,R34,R35,R41,R43,R50,R78,R72,R53,R63",R_0805_2012Metric,C149504
1M (0805W8F1004T5E),"R74,R21,R36,R49,R54,R61",R_0805_2012Metric,C17514
BZT52C15 (BZT52C15-7-F),"D17,D5,D15,D12,D14",D_SOD-123,C177014
BSS138 (BSS138LT1G),"Q12,Q7,Q11,Q10",SOT-23,C82045
USBLC6-2SC6 (USBLC6-2SC6),U8,SOT-23-6,C7519
SHARP LS027B7DH01A (FH12-10S-0.5SH(55)),J7,Hirose_FH12-10S-0.5SH_1x10-1MP_P0.50mm_Horizontal,C506791
CY15B104QN-50SXI (MB85RS4MTPF-G-BCERE1),U1,SOIC-8_5.3x5.3mm_P1.27mm,C42742723
TPS3840PH27 (TPS3840PH27DBVRQ1),U3,SOT-23-5,C1849503
74LVC1G32 (SN74LVC1G32DBVR),U4,SOT-23-5,C10096
100u (LMK325ABJ107MM-P),C13,C_1210_3225Metric,C386065
PRZYCISKI (B5B-XH-A(LF)(SN)),J10,JST_XH_B5B-XH-A_1x05_P2.50mm_Vertical,C157991
CISZA / 12V / OGNIWA 4xAA / WYLACZNIK (B2B-XH-A(LF)(SN)),"J11,J2,J1,J3",JST_XH_B2B-XH-A_1x02_P2.50mm_Vertical,C158012
TPD4E1U06DCKR (TPD4E1U06DCKR),U9,SOT-363_SC-70-6,C194628
TPD1E10B09 (TPD1E10B09DPYR),"D19,D18",Texas_DPY0002A_0.6x1mm_P0.65mm,C88031
PRZYGOTOWANIE (B3F-1000),SW6,SW_TH_Tactile_Omron_B3F-100x,C93157
ALARM (WP7113ID),D1,LED_D5.0mm,C6926004
CEM-1203(42) (CEM-1203(42)),BZ1,MagneticBuzzer_ProSignal_ABT-410-RC,C3812098
22R (1206W4F220JT5E),R2,R_1206_3216Metric,C17958
1N4148W (1N4148W),D2,D_SOD-123,C81598
MMBT3904 (MMBT3904),Q1,SOT-23,C20526
MCP1640 (MCP1640T-I/CHY),U2,SOT-23-6,C44365
4u7 (744031004),L1,L_Wuerth_WE-TPC-3816,C2649331
309k (0805W8F3093T5E),R22,R_0805_2012Metric,C57148
100p (CL21C101JBANNNC),C10,C_0805_2012Metric,C1790
T1A (01110501Z),"F1A,F1B",Fuseholder_Clip-5x20mm_Bel_FC-203-22_Lateral_P17.80x5.00mm_D1.17mm_Horizontal,C151075
SMBJ33CA (SMBJ33CA),D4,D_SMB,C19077587
LM74800-Q1 (LM74800QDRRRQ1),U5,WSON-12-1EP_3x3mm_P0.5mm_EP1.5x2.5mm,C3215600
AO4292E (AO4292E),"Q2,Q3",SOIC-8_3.9x4.9mm_P1.27mm,C176743
100n (CL21B104KCFNNNE),"C30,C38",C_0805_2012Metric,C28233
102k (RT0805BRD07102KL),R30,R_0805_2012Metric,C865126
8k06 (RT0805BRD078K06L),R31,R_0805_2012Metric,C865685
27n (CC0805KRX7R9BB273),C32,C_0805_2012Metric,C113860
SI2309CDS (SI2309CDS-T1-GE3),Q4,SOT-23,C10493
"2N7002 (2N7002,215)",Q5,SOT-23,C65189
221k (AR05BTCW2213),R37,R_0805_2012Metric,C2984388
10n (CL21B103KBANNNC),"C39,C65",C_0805_2012Metric,C1710
10k (RT0805BRD0710KL),"R38,R45",R_0805_2012Metric,C110775
15k4 (RT0805BRD0715K4L),R39,R_0805_2012Metric,C865207
"BAV199 (BAV199,215)","D6,D11",SOT-23,C40919
1R (RC2512FK-071RL),R40,R_2512_6332Metric,C181756
RB168MM-40 (RB168MM-40TR),D7,D_SOD-123F,C509936
"BSS84AK (BSS84AK,215)","Q6,Q8,Q9",SOT-23,C127273
39k (ARG05BTC3902),R44,R_0805_2012Metric,C2828718
"BAS116H (BAS116H,115)","D8,D9,D13",D_SOD-123F,C74210
1k (RC2512FK-071KL),R46,R_2512_6332Metric,C189504
1u (CL21B105KBFNNNE),C35,C_0805_2012Metric,C28323
BZT52C33 (BZT52C33),D10,D_SOD-123,C19077419
LTC2955ITS8-2 (LTC2955ITS8-2#TRPBF),U6,TSOT-23-8,C683797
280k (RT0805BRD07280KL),R70,R_0805_2012Metric,C865351
30k1 (RT0805BRD0730K1L),R71,R_0805_2012Metric,C865392
470n (CL21B474KBFNNNE),C53,C_0805_2012Metric,C13967
2u2 (CL21B225KAFNNNE),C37,C_0805_2012Metric,C19110
470k (0805W8F4703T5E),R48,R_0805_2012Metric,C17709
BZT52C5V1 (BZT52C5V1),D16,D_SOD-123,C19077401
220k (0805W8F2203T5E),"R51,R55",R_0805_2012Metric,C17556
1n (CL21B102KBCNNNC),C52,C_0805_2012Metric,C46653
100u 25V (PXB 25V100 8*11.5),C50,CP_Radial_D8.0mm_P3.50mm,C350221
LTC3115-1 (LTC3115EFE-1#PBF),U7,LTC3115-1_FE20_CA,C580689
15u (SRP1038A-150M),L2,L_Bourns_SRP1038A,C780183
10u (CC1210KKX7R9BB106),"C40,C41",C_1210_3225Metric,C596319
22u (CS3225X5R226K160NRL),"C42,C43",C_1210_3225Metric,C2918506
47k5 (RC0805FR-0747K5L),R60,R_0805_2012Metric,C137519
432k (0805W8F4323T5E),R62,R_0805_2012Metric,C17693
82p (CC0805JRNPO9BN820),"C48,C51",C_0805_2012Metric,C113833
3n9 (CC0805KRX7R9BB392),C49,C_0805_2012Metric,C113861
20k (0805W8F2002T5E),"R67,R68",R_0805_2012Metric,C4328

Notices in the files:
hardware/dev-bench/cad/plytka-nosna.kicad_pcb:
WICI (CERN-OHL-P-2.0)
